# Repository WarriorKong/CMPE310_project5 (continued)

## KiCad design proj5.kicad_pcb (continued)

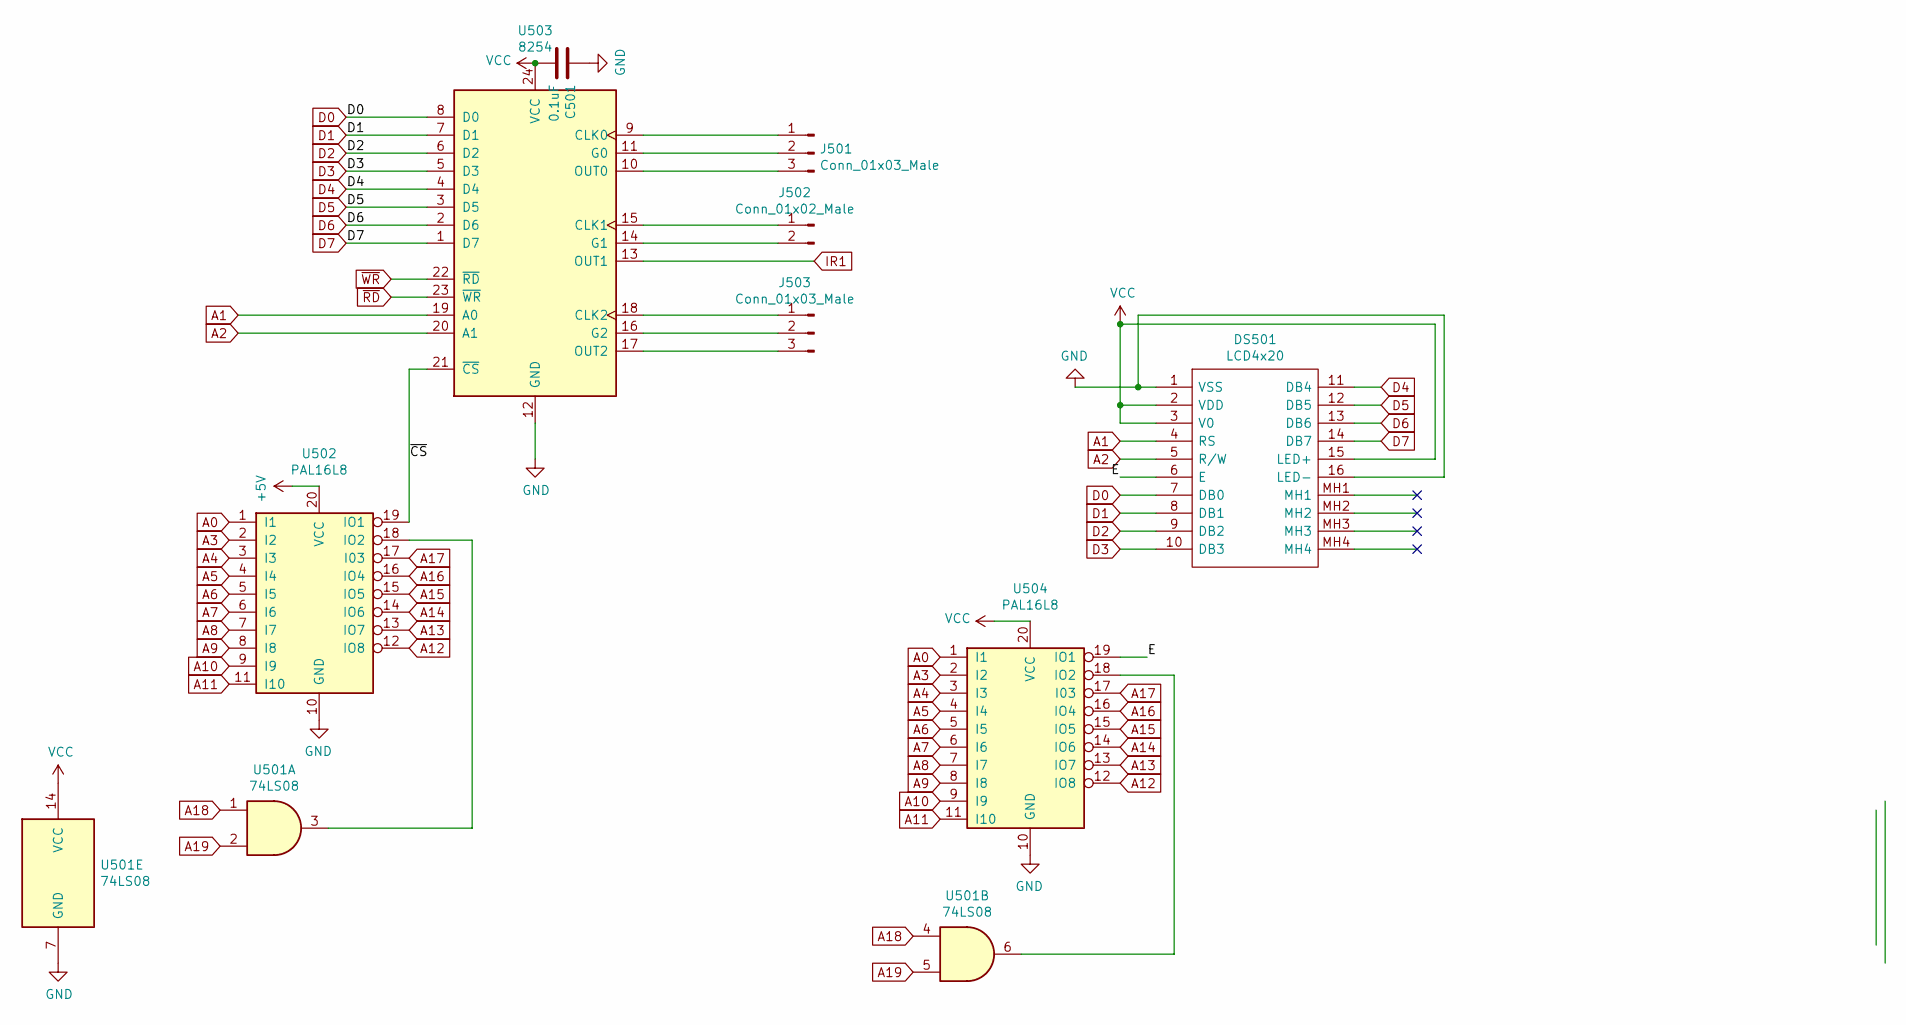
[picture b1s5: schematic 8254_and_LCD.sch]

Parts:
C501: 0.1uF; CP_Elec_3x5.3
DS501: LCD4x20; Mouser Part Number 763-0420AZFLYBW33V3
J501, J503: Conn_01x03_Male; JST_GH_BM03B-GHS-TBT_1x03-1MP_P1.25mm_Vertical
J502: Conn_01x02_Male; JST_GH_BM02B-GHS-TBT_1x02-1MP_P1.25mm_Vertical
U501: 74LS08; DIP-14_W7.62mm_SMDSocket_SmallPads
U502, U504: PAL16L8; DIP-20_W7.62mm_SMDSocket_SmallPads
U503: 8254; DIP-24_W15.24mm

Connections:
+5V: C501.2, DS501.2 (VDD), DS501.3 (V0), DS501.15 (LED+), U501.14 (VCC), U502.20 (VCC), U503.24 (VCC), U504.20 (VCC); also elsewhere on the board
/8254_and_LCD/E: DS501.6 (E), U504.19 (IO1)
/8254_and_LCD/~CS: U502.19 (IO1), U503.21 (~CS~)
A0: U502.1 (I1), U504.1 (I1); also elsewhere on the board
A1: DS501.4 (RS), U503.19 (A0); also elsewhere on the board
A2: DS501.5 (R/W), U503.20 (A1); also elsewhere on the board
A3: U502.2 (I2), U504.2 (I2); also elsewhere on the board
A4: U502.3 (I3), U504.3 (I3); also elsewhere on the board
A5: U502.4 (I4), U504.4 (I4); also elsewhere on the board
A6: U502.5 (I5), U504.5 (I5); also elsewhere on the board
A7: U502.6 (I6), U504.6 (I6); also elsewhere on the board
A8: U502.7 (I7), U504.7 (I7); also elsewhere on the board
A9: U502.8 (I8), U504.8 (I8); also elsewhere on the board
A10: U502.9 (I9), U504.9 (I9); also elsewhere on the board
A11: U502.11 (I10), U504.11 (I10); also elsewhere on the board
A12: U502.12 (IO8), U504.12 (IO8); also elsewhere on the board
A13: U502.13 (IO7), U504.13 (IO7); also elsewhere on the board
A14: U502.14 (IO6), U504.14 (IO6); also elsewhere on the board
A15: U502.15 (IO5), U504.15 (IO5); also elsewhere on the board
A16: U502.16 (IO4), U504.16 (IO4); also elsewhere on the board
A17: U502.17 (I03), U504.17 (I03); also elsewhere on the board
A18: U501.1, U501.4; also elsewhere on the board
A19: U501.2, U501.5; also elsewhere on the board
D0: DS501.7 (DB0), U503.8 (D0); also elsewhere on the board
D1: DS501.8 (DB1), U503.7 (D1); also elsewhere on the board
D2: DS501.9 (DB2), U503.6 (D2); also elsewhere on the board
D3: DS501.10 (DB3), U503.5 (D3); also elsewhere on the board
D4: DS501.11 (DB4), U503.4 (D4); also elsewhere on the board
D5: DS501.12 (DB5), U503.3 (D5); also elsewhere on the board
D6: DS501.13 (DB6), U503.2 (D6); also elsewhere on the board
D7: DS501.14 (DB7), U503.1 (D7); also elsewhere on the board
GND: C501.1, DS501.1 (VSS), DS501.16 (LED-), U501.7 (GND), U502.10 (GND), U503.12 (GND), U504.10 (GND); also elsewhere on the board
IR1: U503.13 (OUT1); also elsewhere on the board
unnamed: J501.1, U503.9 (CLK0)
unnamed: J501.2, U503.11 (G0)
unnamed: J501.3, U503.10 (OUT0)
unnamed: J502.1, U503.15 (CLK1)
unnamed: J502.2, U503.14 (G1)
unnamed: J503.1, U503.18 (CLK2)
unnamed: J503.2, U503.16 (G2)
unnamed: J503.3, U503.17 (OUT2)
unnamed: U501.3, U502.18 (IO2)
unnamed: U501.6, U504.18 (IO2)
~RD: U503.23 (~WR~); also elsewhere on the board
~WR: U503.22 (~RD~); also elsewhere on the board

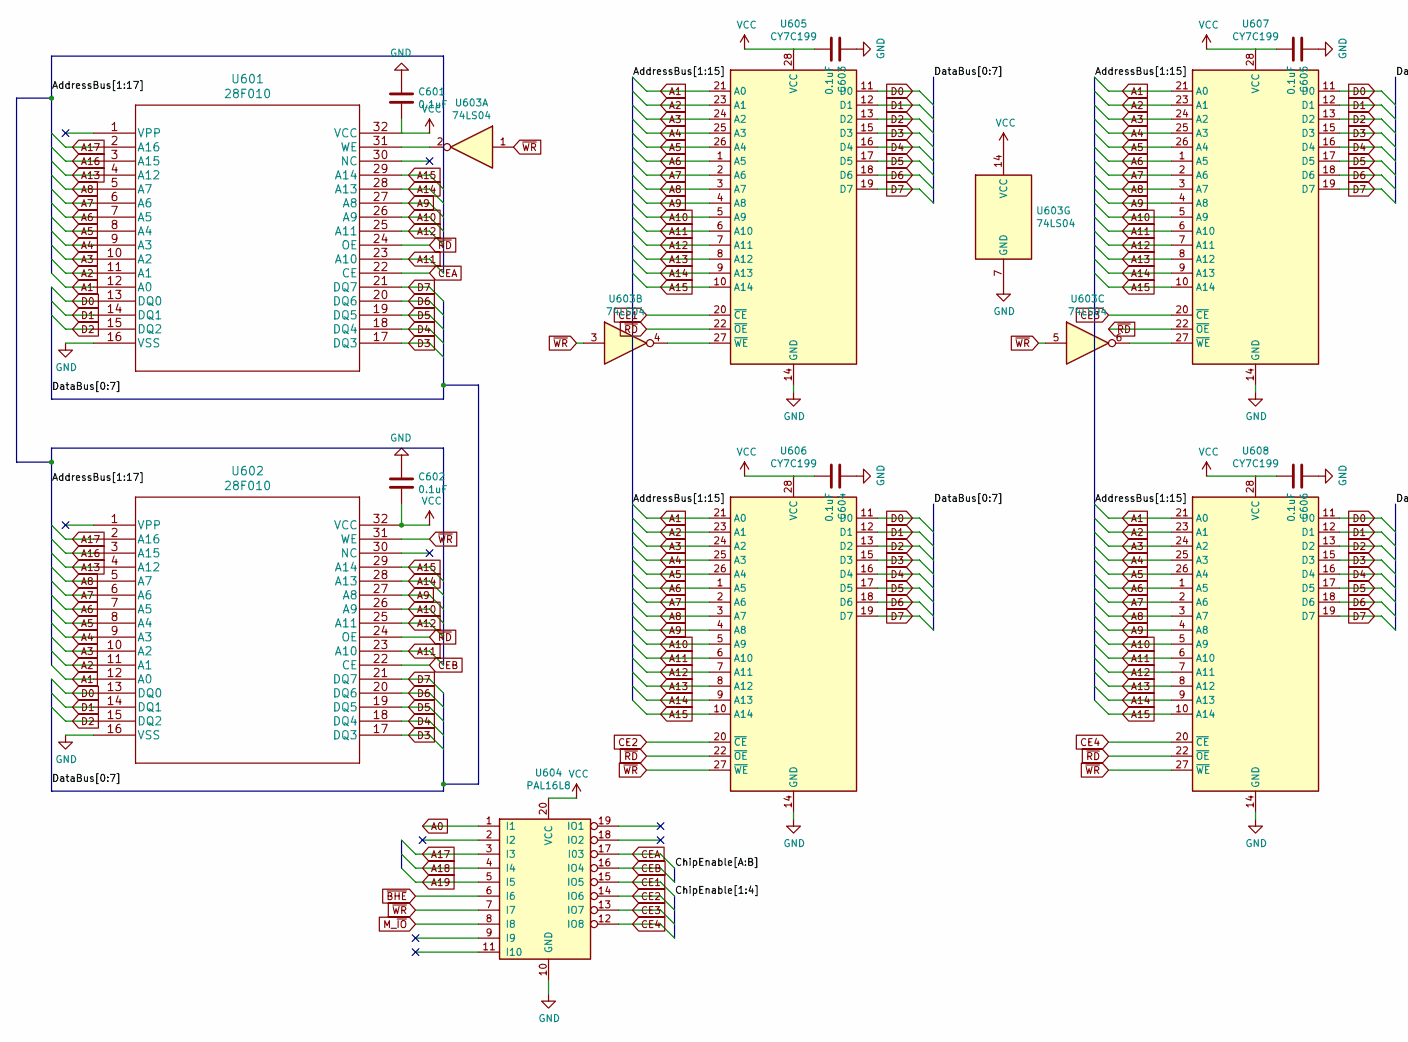
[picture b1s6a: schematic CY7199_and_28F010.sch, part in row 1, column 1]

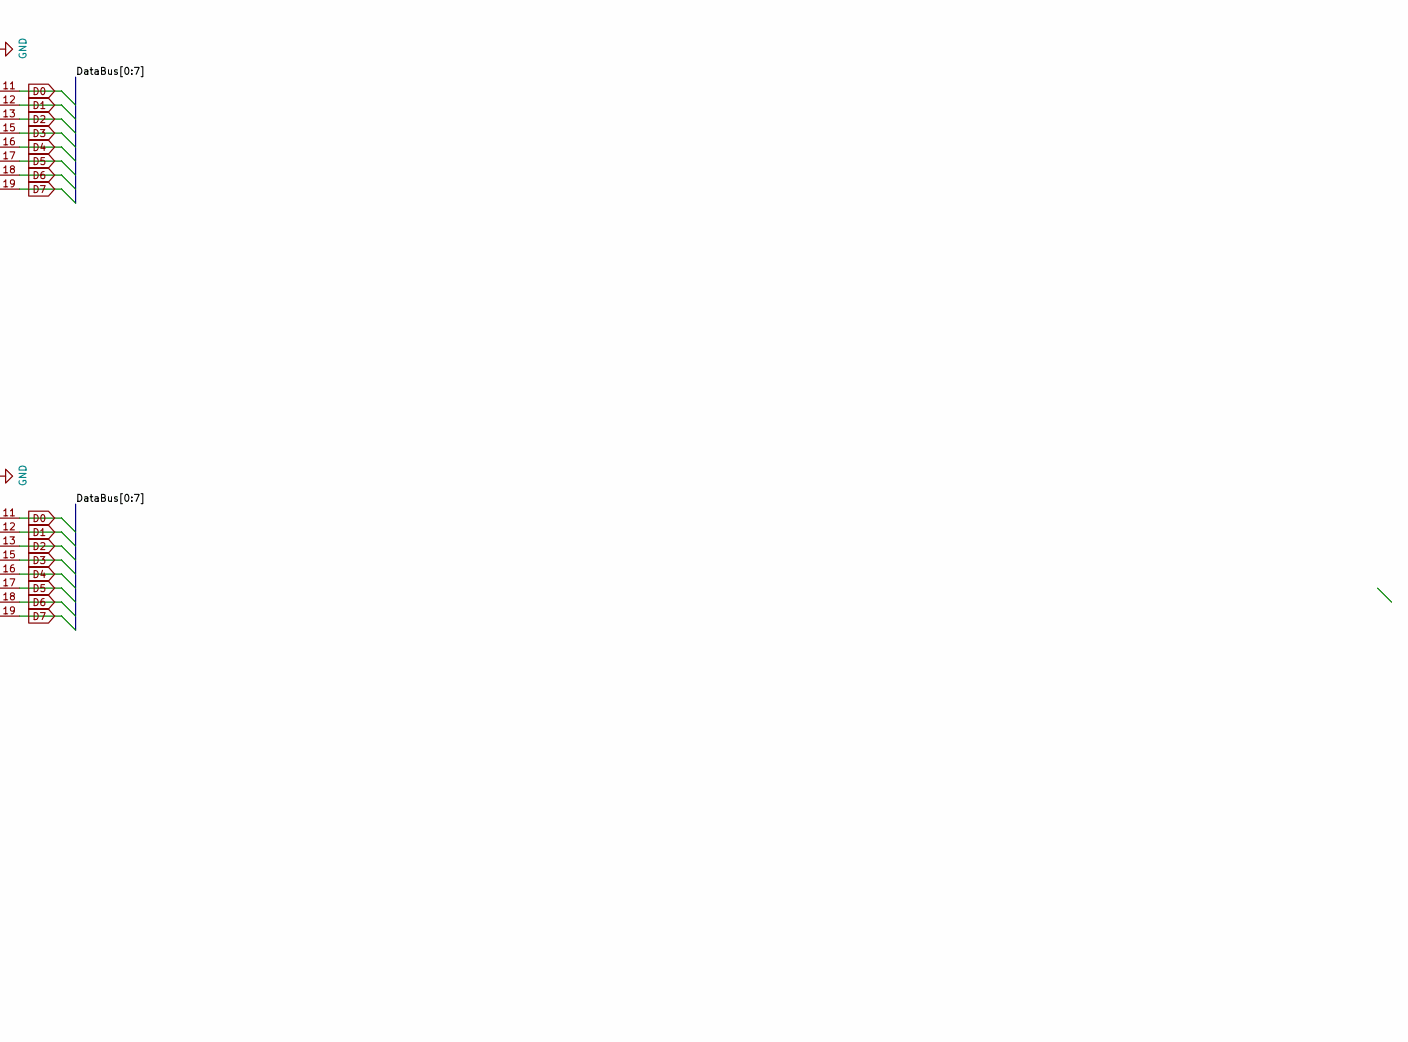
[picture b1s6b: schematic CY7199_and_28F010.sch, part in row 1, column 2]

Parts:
C601, C602, C603, C604, C605, C606: 0.1uF; CP_Elec_3x5.3
U601, U602: 28F010
U603: 74LS04; DIP-14_W7.62mm_SMDSocket_SmallPads
U604: PAL16L8; DIP-20_W7.62mm_SMDSocket_SmallPads
U605, U606, U607, U608: CY7C199; DIP-28_W7.62mm_SMDSocket_SmallPads

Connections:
+5V: C601.2, C602.2, C603.2, C604.2, C605.2, C606.2, U601.32 (VCC), U602.32 (VCC), U603.14 (VCC), U604.20 (VCC), U605.28 (VCC), U606.28 (VCC), U607.28 (VCC), U608.28 (VCC); also elsewhere on the board
A0: U604.1 (I1); also elsewhere on the board
A1: U601.12 (A0), U602.12 (A0), U605.21 (A0), U606.21 (A0), U607.21 (A0), U608.21 (A0); also elsewhere on the board
A2: U601.11 (A1), U602.11 (A1), U605.23 (A1), U606.23 (A1), U607.23 (A1), U608.23 (A1); also elsewhere on the board
A3: U601.10 (A2), U602.10 (A2), U605.24 (A2), U606.24 (A2), U607.24 (A2), U608.24 (A2); also elsewhere on the board
A4: U601.9 (A3), U602.9 (A3), U605.25 (A3), U606.25 (A3), U607.25 (A3), U608.25 (A3); also elsewhere on the board
A5: U601.8 (A4), U602.8 (A4), U605.26 (A4), U606.26 (A4), U607.26 (A4), U608.26 (A4); also elsewhere on the board
A6: U601.7 (A5), U602.7 (A5), U605.1 (A5), U606.1 (A5), U607.1 (A5), U608.1 (A5); also elsewhere on the board
A7: U601.6 (A6), U602.6 (A6), U605.2 (A6), U606.2 (A6), U607.2 (A6), U608.2 (A6); also elsewhere on the board
A8: U601.5 (A7), U602.5 (A7), U605.3 (A7), U606.3 (A7), U607.3 (A7), U608.3 (A7); also elsewhere on the board
A9: U601.27 (A8), U602.27 (A8), U605.4 (A8), U606.4 (A8), U607.4 (A8), U608.4 (A8); also elsewhere on the board
A10: U601.26 (A9), U602.26 (A9), U605.5 (A9), U606.5 (A9), U607.5 (A9), U608.5 (A9); also elsewhere on the board
A11: U601.23 (A10), U602.23 (A10), U605.6 (A10), U606.6 (A10), U607.6 (A10), U608.6 (A10); also elsewhere on the board
A12: U601.25 (A11), U602.25 (A11), U605.7 (A11), U606.7 (A11), U607.7 (A11), U608.7 (A11); also elsewhere on the board
A13: U601.4 (A12), U602.4 (A12), U605.8 (A12), U606.8 (A12), U607.8 (A12), U608.8 (A12); also elsewhere on the board
A14: U601.28 (A13), U602.28 (A13), U605.9 (A13), U606.9 (A13), U607.9 (A13), U608.9 (A13); also elsewhere on the board
A15: U601.29 (A14), U602.29 (A14), U605.10 (A14), U606.10 (A14), U607.10 (A14), U608.10 (A14); also elsewhere on the board
A16: U601.3 (A15), U602.3 (A15); also elsewhere on the board
A17: U601.2 (A16), U602.2 (A16), U604.3 (I3); also elsewhere on the board
A18: U604.4 (I4); also elsewhere on the board
A19: U604.5 (I5); also elsewhere on the board
CE1: U604.15 (IO5), U605.20 (~CE~)
CE2: U604.14 (IO6), U606.20 (~CE~)
CE3: U604.13 (IO7), U607.20 (~CE~)
CE4: U604.12 (IO8), U608.20 (~CE~)
CEA: U601.22 (CE), U604.17 (I03)
CEB: U602.22 (CE), U604.16 (IO4)
D0: U601.13 (DQ0), U602.13 (DQ0), U605.11 (D0), U606.11 (D0), U607.11 (D0), U608.11 (D0); also elsewhere on the board
D1: U601.14 (DQ1), U602.14 (DQ1), U605.12 (D1), U606.12 (D1), U607.12 (D1), U608.12 (D1); also elsewhere on the board
D2: U601.15 (DQ2), U602.15 (DQ2), U605.13 (D2), U606.13 (D2), U607.13 (D2), U608.13 (D2); also elsewhere on the board
D3: U601.17 (DQ3), U602.17 (DQ3), U605.15 (D3), U606.15 (D3), U607.15 (D3), U608.15 (D3); also elsewhere on the board
D4: U601.18 (DQ4), U602.18 (DQ4), U605.16 (D4), U606.16 (D4), U607.16 (D4), U608.16 (D4); also elsewhere on the board
D5: U601.19 (DQ5), U602.19 (DQ5), U605.17 (D5), U606.17 (D5), U607.17 (D5), U608.17 (D5); also elsewhere on the board
D6: U601.20 (DQ6), U602.20 (DQ6), U605.18 (D6), U606.18 (D6), U607.18 (D6), U608.18 (D6); also elsewhere on the board
D7: U601.21 (DQ7), U602.21 (DQ7), U605.19 (D7), U606.19 (D7), U607.19 (D7), U608.19 (D7); also elsewhere on the board
GND: C601.1, C602.1, C603.1, C604.1, C605.1, C606.1, U601.16 (VSS), U602.16 (VSS), U603.7 (GND), U604.10 (GND), U605.14 (GND), U606.14 (GND), U607.14 (GND), U608.14 (GND); also elsewhere on the board
M_~IO: U604.8 (I8); also elsewhere on the board
unnamed: U601.31 (WE), U603.2
unnamed: U603.4, U605.27 (~WE~)
unnamed: U603.6, U607.27 (~WE~)
~BHE: U604.6 (I6); also elsewhere on the board
~RD: U601.24 (OE), U602.24 (OE), U605.22 (~OE~), U606.22 (~OE~), U607.22 (~OE~), U608.22 (~OE~); also elsewhere on the board
~WR: U602.31 (WE), U603.1, U603.3, U603.5, U604.7 (I7), U606.27 (~WE~), U608.27 (~WE~); also elsewhere on the board

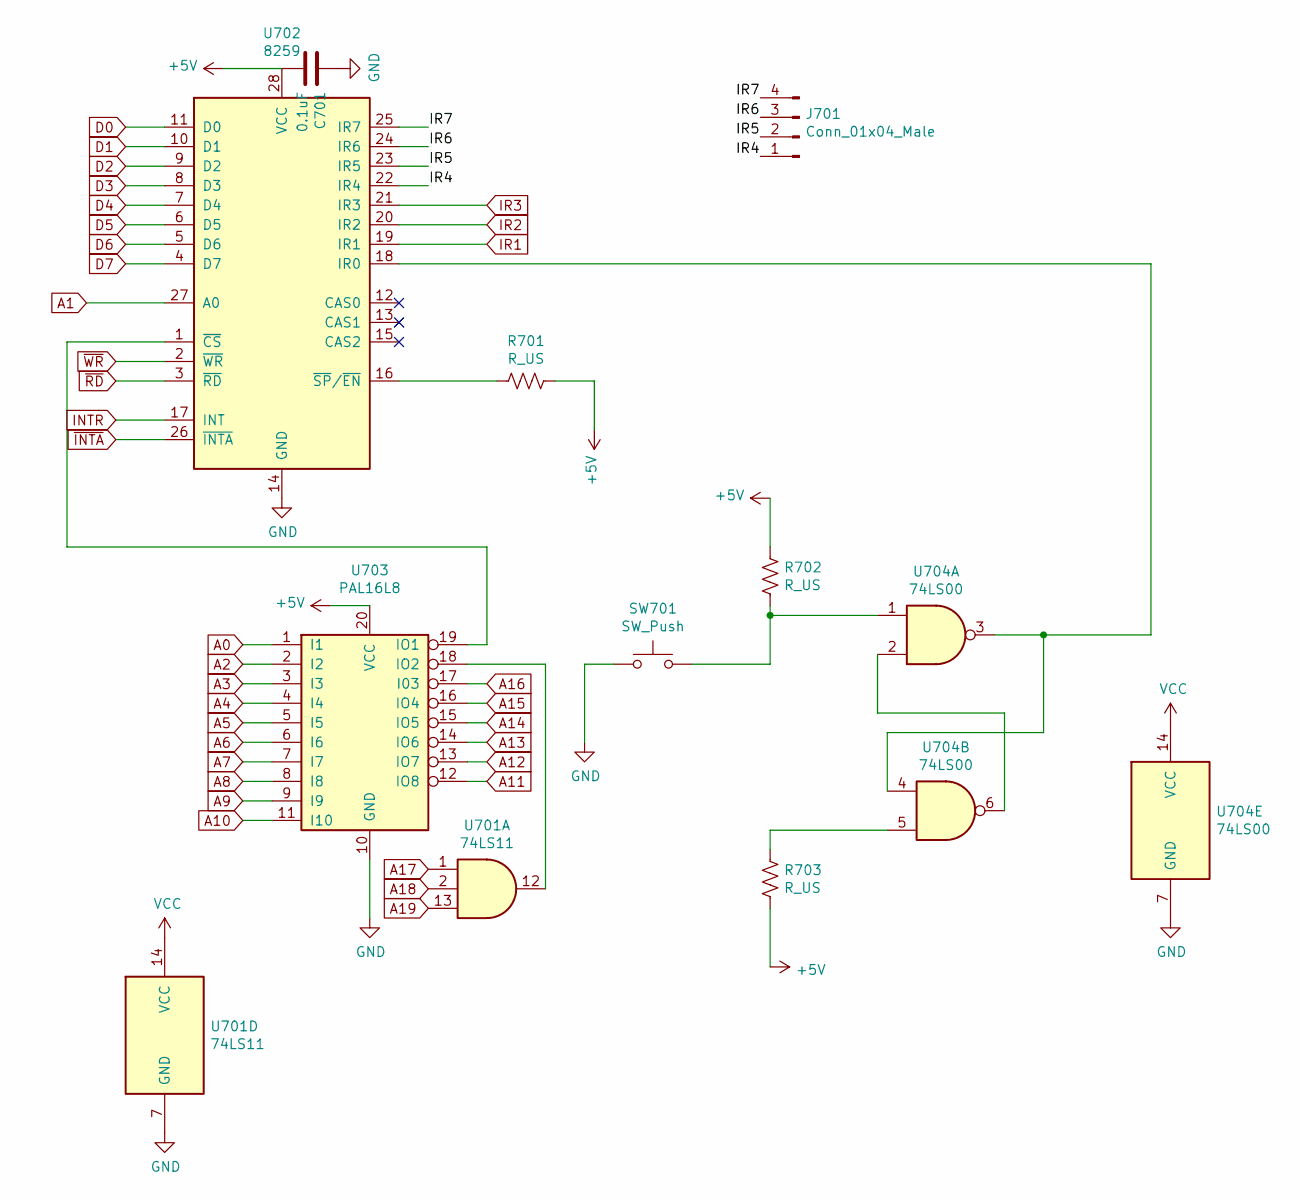
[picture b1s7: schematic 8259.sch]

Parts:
C701: 0.1uF; CP_Elec_3x5.3
J701: Conn_01x04_Male; JST_GH_BM04B-GHS-TBT_1x04-1MP_P1.25mm_Vertical
R701, R702, R703: R_US; R_0402_1005Metric
SW701: SW_Push; SW_SPST_B3U-1000P
U701: 74LS11; DIP-14_W7.62mm_SMDSocket_SmallPads
U702: 8259; DIP-28_W15.24mm
U703: PAL16L8; DIP-20_W7.62mm_SMDSocket_SmallPads
U704: 74LS00; DIP-14_W7.62mm_SMDSocket_SmallPads

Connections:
+5V: C701.2, R701.1, R702.1, R703.2, U701.14 (VCC), U702.28 (VCC), U703.20 (VCC), U704.14 (VCC); also elsewhere on the board
/8259/IR4: J701.1, U702.22 (IR4)
/8259/IR5: J701.2, U702.23 (IR5)
/8259/IR6: J701.3, U702.24 (IR6)
/8259/IR7: J701.4, U702.25 (IR7)
A0: U703.1 (I1); also elsewhere on the board
A1: U702.27 (A0); also elsewhere on the board
A2: U703.2 (I2); also elsewhere on the board
A3: U703.3 (I3); also elsewhere on the board
A4: U703.4 (I4); also elsewhere on the board
A5: U703.5 (I5); also elsewhere on the board
A6: U703.6 (I6); also elsewhere on the board
A7: U703.7 (I7); also elsewhere on the board
A8: U703.8 (I8); also elsewhere on the board
A9: U703.9 (I9); also elsewhere on the board
A10: U703.11 (I10); also elsewhere on the board
A11: U703.12 (IO8); also elsewhere on the board
A12: U703.13 (IO7); also elsewhere on the board
A13: U703.14 (IO6); also elsewhere on the board
A14: U703.15 (IO5); also elsewhere on the board
A15: U703.16 (IO4); also elsewhere on the board
A16: U703.17 (I03); also elsewhere on the board
A17: U701.1; also elsewhere on the board
A18: U701.2; also elsewhere on the board
A19: U701.13; also elsewhere on the board
D0: U702.11 (D0); also elsewhere on the board
D1: U702.10 (D1); also elsewhere on the board
D2: U702.9 (D2); also elsewhere on the board
D3: U702.8 (D3); also elsewhere on the board
D4: U702.7 (D4); also elsewhere on the board
D5: U702.6 (D5); also elsewhere on the board
D6: U702.5 (D6); also elsewhere on the board
D7: U702.4 (D7); also elsewhere on the board
GND: C701.1, SW701.1, U701.7 (GND), U702.14 (GND), U703.10 (GND), U704.7 (GND); also elsewhere on the board
INTR: U702.17 (INT); also elsewhere on the board
IR1: U702.19 (IR1); also elsewhere on the board
IR2: U702.20 (IR2); also elsewhere on the board
IR3: U702.21 (IR3); also elsewhere on the board
unnamed: R701.2, U702.16 (~SP~/~EN~)
unnamed: R702.2, SW701.2, U704.1
unnamed: R703.1, U704.5
unnamed: U701.12, U703.18 (IO2)
unnamed: U702.1 (~CS~), U703.19 (IO1)
unnamed: U702.18 (IR0), U704.3, U704.4
unnamed: U704.2, U704.6
~INTA: U702.26 (~INTA~); also elsewhere on the board
~RD: U702.3 (~RD~); also elsewhere on the board
~WR: U702.2 (~WR~); also elsewhere on the board

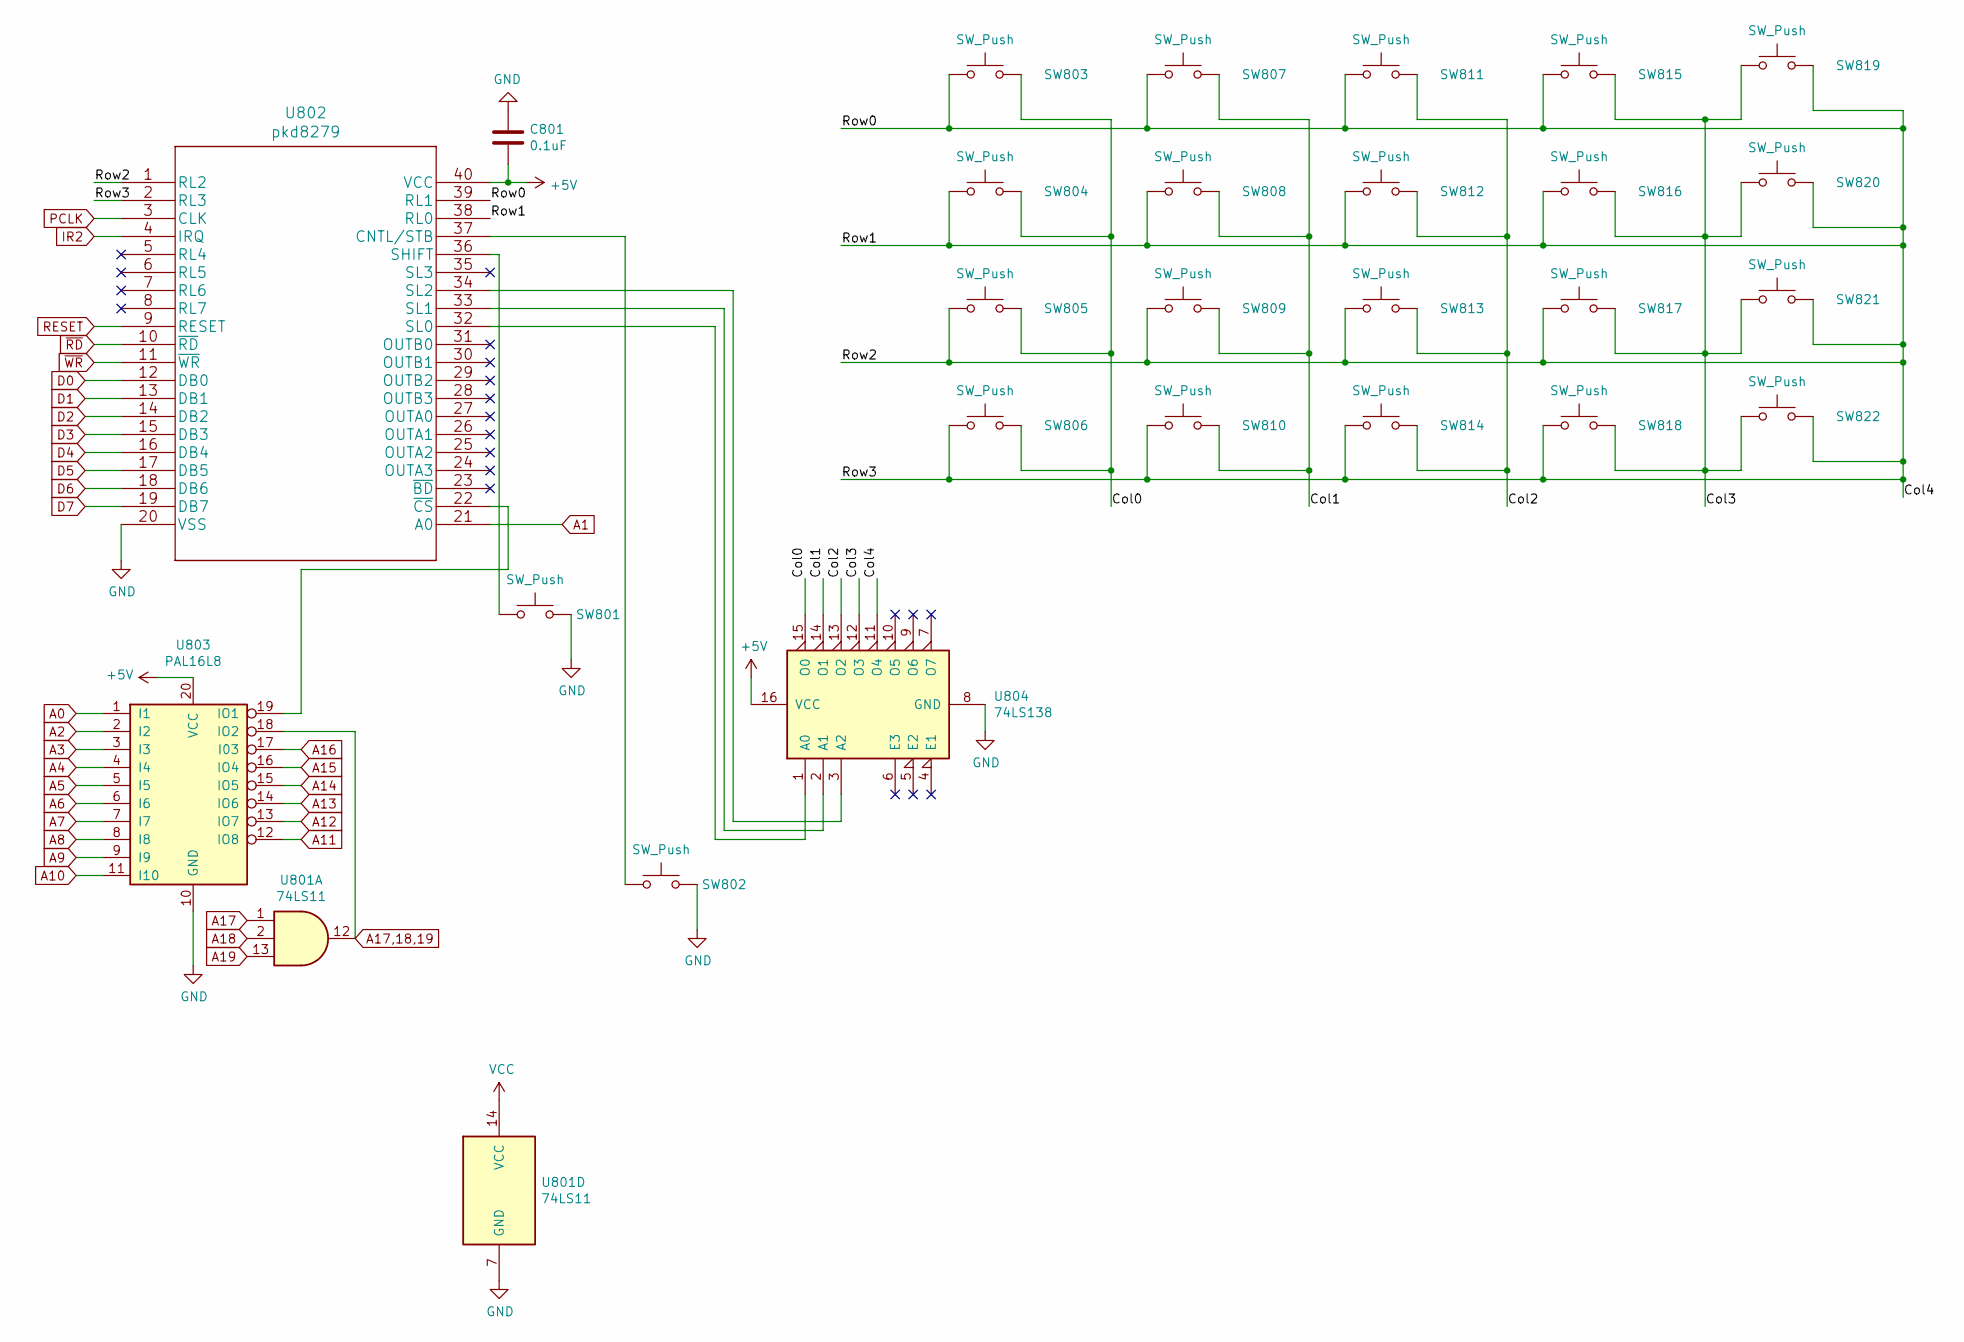
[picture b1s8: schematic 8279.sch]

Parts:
C801: 0.1uF; CP_Elec_3x5.3
SW801, SW802, SW803, SW804, SW805, SW806, SW807, SW808, SW809, SW810, SW811, SW812, SW813, SW814, SW815, SW816, SW817, SW818, SW819, SW820, SW821, SW822: SW_Push; SW_SPST_B3U-1000P
U801: 74LS11; DIP-14_W7.62mm_SMDSocket_SmallPads
U802: pkd8279
U803: PAL16L8; DIP-20_W7.62mm_SMDSocket_SmallPads
U804: 74LS138; DIP-16_W7.62mm_SMDSocket_SmallPads

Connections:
+5V: C801.2, U801.14 (VCC), U802.40 (VCC), U803.20 (VCC), U804.16 (VCC); also elsewhere on the board
/8279/Col0: SW803.2, SW804.2, SW805.2, SW806.2, U804.15 (O0)
/8279/Col1: SW807.2, SW808.2, SW809.2, SW810.2, U804.14 (O1)
/8279/Col2: SW811.2, SW812.2, SW813.2, SW814.2, U804.13 (O2)
/8279/Col3: SW815.2, SW816.2, SW817.2, SW818.2, SW819.1, SW820.1, SW821.1, SW822.1, U804.12 (O3)
/8279/Col4: SW803.1, SW804.1, SW805.1, SW806.1, SW807.1, SW808.1, SW809.1, SW810.1, SW811.1, SW812.1, SW813.1, SW814.1, SW815.1, SW816.1, SW817.1, SW818.1, SW819.2, SW820.2, SW821.2, SW822.2, U802.1 (RL2), U802.2 (RL3), U802.38 (RL0), U802.39 (RL1), U804.11 (O4)
A0: U803.1 (I1); also elsewhere on the board
A1: U802.21 (A0); also elsewhere on the board
A2: U803.2 (I2); also elsewhere on the board
A3: U803.3 (I3); also elsewhere on the board
A4: U803.4 (I4); also elsewhere on the board
A5: U803.5 (I5); also elsewhere on the board
A6: U803.6 (I6); also elsewhere on the board
A7: U803.7 (I7); also elsewhere on the board
A8: U803.8 (I8); also elsewhere on the board
A9: U803.9 (I9); also elsewhere on the board
A10: U803.11 (I10); also elsewhere on the board
A11: U803.12 (IO8); also elsewhere on the board
A12: U803.13 (IO7); also elsewhere on the board
A13: U803.14 (IO6); also elsewhere on the board
A14: U803.15 (IO5); also elsewhere on the board
A15: U803.16 (IO4); also elsewhere on the board
A16: U803.17 (I03); also elsewhere on the board
A17: U801.1; also elsewhere on the board
A17,18,19: U801.12, U803.18 (IO2); also elsewhere on the board
A18: U801.2; also elsewhere on the board
A19: U801.13; also elsewhere on the board
D0: U802.12 (DB0); also elsewhere on the board
D1: U802.13 (DB1); also elsewhere on the board
D2: U802.14 (DB2); also elsewhere on the board
D3: U802.15 (DB3); also elsewhere on the board
D4: U802.16 (DB4); also elsewhere on the board
D5: U802.17 (DB5); also elsewhere on the board
D6: U802.18 (DB6); also elsewhere on the board
D7: U802.19 (DB7); also elsewhere on the board
GND: C801.1, SW801.2, SW802.2, U801.7 (GND), U802.20 (VSS), U803.10 (GND), U804.8 (GND); also elsewhere on the board
IR2: U802.4 (IRQ); also elsewhere on the board
unnamed: SW801.1, U802.36 (SHIFT)
unnamed: SW802.1, U802.37 (CNTL/STB)
unnamed: U802.22 (~CS), U803.19 (IO1)
unnamed: U802.32 (SL0), U804.1 (A0)
unnamed: U802.33 (SL1), U804.2 (A1)
unnamed: U802.34 (SL2), U804.3 (A2)
PCLK: U802.3 (CLK); also elsewhere on the board
RESET: U802.9 (RESET); also elsewhere on the board
~RD: U802.10 (~RD); also elsewhere on the board
~WR: U802.11 (~WR); also elsewhere on the board

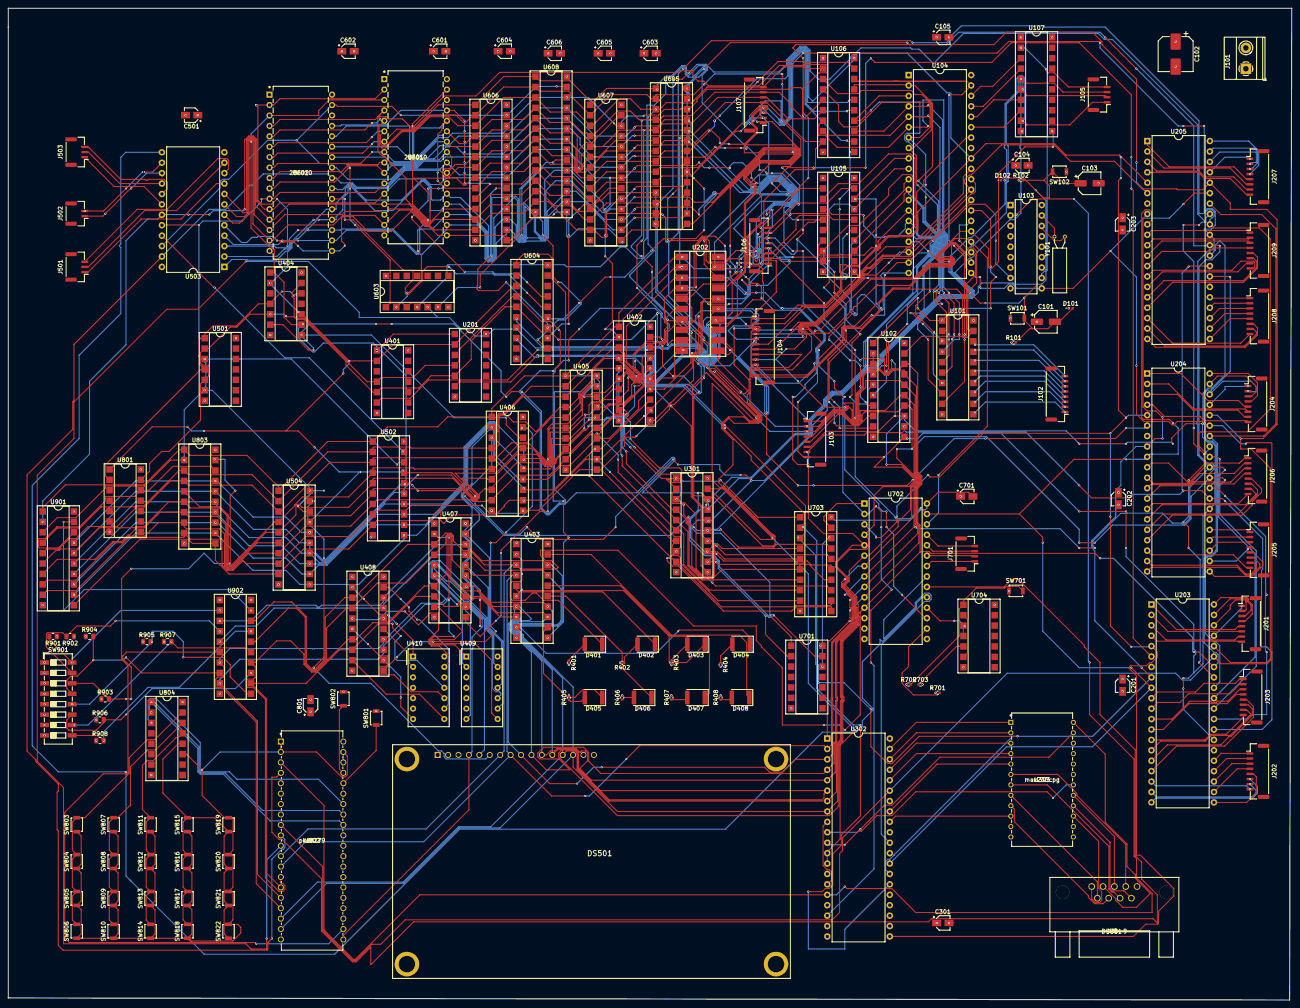
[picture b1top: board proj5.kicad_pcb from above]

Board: 4 copper layers, 312.9 x 241.8 mm, 145 parts (0 on the bottom side), 266 nets.

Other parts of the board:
R901, R902, R903, R904, R905, R906, R907, R908: R_US; R_0805_2012Metric
SW901: SW_DIP_x08; SW_DIP_SPSTx08_Slide_6.7x21.88mm_W6.73mm_P2.54mm_LowProfile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
U901: PAL16L8; DIP-20_W7.62mm_SMDSocket_SmallPads
U902: 74LS244; DIP-20_W7.62mm_SMDSocket_SmallPads

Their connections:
+5V: R901.1, R902.1, R903.1, R904.1, R905.1, R906.1, R907.1, R908.1, U901.20, U902.20; also elsewhere on the board
A0: U901.1; also elsewhere on the board
A1: U901.2; also elsewhere on the board
A2: U901.3; also elsewhere on the board
A3: U901.4; also elsewhere on the board
A4: U901.5; also elsewhere on the board
A6: U901.6; also elsewhere on the board
A7: U901.7; also elsewhere on the board
A8: U901.8; also elsewhere on the board
A9: U901.9; also elsewhere on the board
A10: U901.11; also elsewhere on the board
A11: U901.12; also elsewhere on the board
A12: U901.13; also elsewhere on the board
A13: U901.14; also elsewhere on the board
A14: U901.15; also elsewhere on the board
A15: U901.16; also elsewhere on the board
A16: U901.17; also elsewhere on the board
A17,18,19: U901.18; also elsewhere on the board
D0: U902.18; also elsewhere on the board
D1: U902.16; also elsewhere on the board
D2: U902.14; also elsewhere on the board
D3: U902.12; also elsewhere on the board
D4: U902.9; also elsewhere on the board
D5: U902.7; also elsewhere on the board
D6: U902.5; also elsewhere on the board
D7: U902.3; also elsewhere on the board
GND: SW901.1, SW901.2, SW901.3, SW901.4, SW901.5, SW901.6, SW901.7, SW901.8, U901.10, U902.1, U902.10; also elsewhere on the board
unnamed: R901.2, SW901.16, U902.2
unnamed: R902.2, SW901.15, U902.4
unnamed: R903.2, SW901.14, U902.6
unnamed: R904.2, SW901.13, U902.8
unnamed: R905.2, SW901.12, U902.11
unnamed: R906.2, SW901.11, U902.13
unnamed: R907.2, SW901.10, U902.15
unnamed: R908.2, SW901.9, U902.17
unnamed: U901.19, U902.19

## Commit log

2021-05-06 Adding 2 7 segment LED displays and the 8 LED;s
2021-05-06 Adding 8254 and LCD schematic
    -Dennis Mayher
2021-05-06 adding changes
2021-05-06 updated 8254 and LCD file
    Fixed the A1->RS and A2->R/W
2021-05-06 cleaned up
2021-05-06 tweeked cy7119_and_28f010.sch
2021-05-06 added folder for Component Screenshots
    You can add your screenshots of components to stay organized.
2021-05-06 Updated 7seg&led wiring
    The 8 LEDs power wasn't connected and the OE to ground.
2021-05-06 Updated 7-segLEd screenshot
    Fixed wiring issue
2021-05-06 tweaked a few things
2021-05-06 Create testingupload
2021-05-06 Rename 310 Lab 5.sch to 8259.sch
2021-05-06 Rename Keyboard.sch to 8279.sch
2021-05-06 made some modifications
2021-05-09 made final adjustments to all the designes
2021-05-10 adjusted and incorperated 8dipswitch to pcb
2021-05-10 Added Screenshots of 8254 and LCD display
2021-05-10 Fixed Pins on 8254
    Switched RD and WR global pins on 8254
2021-05-10 8254 RD and WR pin switch
2021-05-11 finished pcb layout
2021-05-12 updated Screenshots for LEDS
